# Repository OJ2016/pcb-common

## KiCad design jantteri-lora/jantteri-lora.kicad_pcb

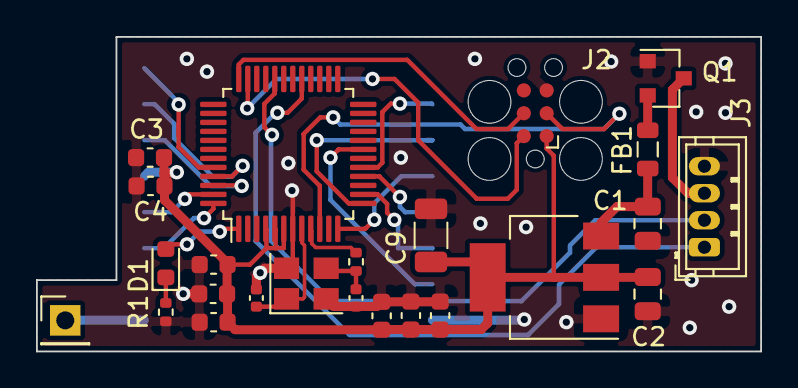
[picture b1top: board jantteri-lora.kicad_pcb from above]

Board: 2 copper layers, 40.2 x 17.5 mm, 25 parts (1 on the bottom side), 27 nets.

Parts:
C1, C2: 10u; C_0805_2012Metric
C3, C4, C10, C11, C12, C13, C14, C15: 100n; C_0603_1608Metric
C9: 4u7; C_1206_3216Metric
C16, C17: 12p; C_0402_1005Metric
D1: LED; LED_0603_1608Metric
FB1: GZ2012D101TF; L_0805_2012Metric
J1: ANT; PinHeader_1x01_P2.54mm_Vertical
J2: Conn_02x03_Odd_Even; Tag-Connect_TC2030-IDC-FP_2x03_P1.27mm_Vertical
J3: DBG; JST_ZH_B4B-ZR_1x04_P1.50mm_Vertical
Q1: IRLML6402TRPBF; SOT-23
R1: 1k5; R_0402_1005Metric
R2: 47; R_0402_1005Metric
U2: AMS1117-3.3; SOT-223-3_TabPin2
U3: RFM95W-868S2; HOPERF_RFM9XW_SMD
U6: STM32G030C8T6; LQFP-48_7x7mm_P0.5mm
Y1: 16MHz; Crystal_SMD_3225-4Pin_3.2x2.5mm

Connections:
+3V3: C2.1, C3.1, C4.1, C9.1, C10.1, C11.1, C12.1, C13.1, C14.1, C15.1, J2.1, U2.2, U3.13, U6.4, U6.5, U6.6
/AMS1117-3.3/VIN: C1.1, FB1.1, U2.3
/STM32G030C8T6/HSE_IN: C16.1, U6.8, Y1.1
/STM32G030C8T6/HSE_OUT: R2.1, U6.9
/STM32G030C8T6/NRST: J2.3, U6.10
/STM32G030C8T6/SWCLK: J2.4, U6.36
/STM32G030C8T6/SWDIO: J2.2, U6.35
DBG_RX: J3.2, U6.32
DBG_TX: J3.1, U6.29
GND: C1.2, C2.2, C3.2, C4.2, C9.2, C10.2, C11.2, C12.2, C13.2, C14.2, C15.2, C16.2, C17.2, J2.5, J3.4, Q1.1, R1.1, U2.1, U3.1, U3.8, U3.10, U6.7, Y1.2, Y1.4
unnamed: C17.1, R2.2, Y1.3
unnamed: D1.1, R1.2
unnamed: D1.2, U6.1
unnamed: FB1.2, Q1.2
unnamed: J1.1, U3.9
RFM_DIO0: U3.14, U6.46
RFM_DIO1: U3.15, U6.45
RFM_DIO2: U3.16, U6.44
RFM_DIO3: U3.11, U6.48
RFM_DIO4: U3.12, U6.47
RFM_DIO5: U3.7, U6.19
RFM_NSS: U3.5, U6.16
RFM_RST: U3.6, U6.14
SPI1_MISO: U3.2, U6.17
SPI1_MOSI: U3.3, U6.13
SPI1_SCK: U3.4, U6.12
USB-5V: J3.3, Q1.3

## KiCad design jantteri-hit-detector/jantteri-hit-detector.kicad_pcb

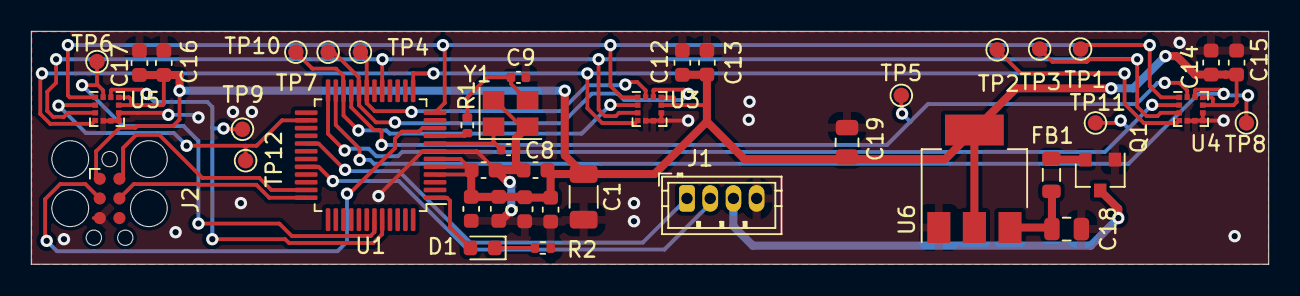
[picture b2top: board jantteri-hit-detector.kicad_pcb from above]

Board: 2 copper layers, 79.9 x 15.0 mm, 42 parts (0 on the bottom side), 27 nets.

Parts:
C1: 4u7; C_1206_3216Metric
C2, C3, C4, C5, C6, C7, C12, C13, C14, C15, C16, C17: 100n; C_0603_1608Metric
C8, C9: 12p; C_0402_1005Metric
C18, C19: 10u; C_0805_2012Metric
D1: LED; LED_0603_1608Metric
FB1: GZ2012D101TF; L_0805_2012Metric
J1: Conn_01x04_Male; JST_ZH_B4B-ZR_1x04_P1.50mm_Vertical
J2: Conn_02x03_Odd_Even; Tag-Connect_TC2030-IDC-FP_2x03_P1.27mm_Vertical
Q1: IRLML6402TRPBF; SOT-23
R1: 47; R_0402_1005Metric
R2: 1k5; R_0402_1005Metric
TP1, TP2, TP3, TP4, TP5, TP6, TP7, TP8, TP9, TP10, TP11, TP12: TestPoint; TestPoint_Pad_D1.0mm
U1: STM32G030C8T6; LQFP-48_7x7mm_P0.5mm
U3, U4, U5: LIS2DW12TR; LGA-12_2x2mm_P0.5mm
U6: AMS1117-3.3; SOT-223-3_TabPin2
Y1: 16MHz; Crystal_SMD_3225-4Pin_3.2x2.5mm

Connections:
+3V3: C1.1, C2.1, C3.1, C4.1, C5.1, C6.1, C7.1, C12.1, C13.1, C14.1, C15.1, C16.1, C17.1, C19.1, J2.1, U1.4 (VBAT), U1.5 (VREF+), U1.6 (VDD/VDDA), U3.9 (VDD), U3.10 (VDD_IO), U4.9 (VDD), U4.10 (VDD_IO), U5.9 (VDD), U5.10 (VDD_IO), U6.2 (VO)
/AMS1117-3.3/VIN: C18.1, FB1.1, U6.3 (VI)
/STM32G030C8T6/HSE_IN: C8.1, U1.8 (PF0-OSC_IN), Y1.1
/STM32G030C8T6/HSE_OUT: R1.1, U1.9 (PF1-OSC_OUT)
/STM32G030C8T6/NRST: J2.3, U1.10 (NRST)
/STM32G030C8T6/SWCLK: J2.4, U1.36 (PA14-BOOT0_(SWCLK))
/STM32G030C8T6/SWDIO: J2.2, U1.35 (PA13_(SWDIO))
GND: C1.2, C2.2, C3.2, C4.2, C5.2, C6.2, C7.2, C8.2, C9.2, C12.2, C13.2, C14.2, C15.2, C16.2, C17.2, C18.2, C19.2, J1.4, J2.5, Q1.1 (G), R2.1, U1.7 (VSS/VSSA), U3.5 (NC), U3.6 (GND), U3.7 (RES), U3.8 (GND), U4.5 (NC), U4.6 (GND), U4.7 (RES), U4.8 (GND), U5.5 (NC), U5.6 (GND), U5.7 (RES), U5.8 (GND), U6.1 (GND), Y1.2, Y1.4
HIT_RX: J1.2, U1.32 (PA10)
HIT_TX: J1.1, U1.29 (PA9)
KX1_CS: TP10.1, U1.22 (PB10), U3.2 (CS)
KX1_INT1: TP4.1, U1.19 (PB0), U3.12 (INT1)
KX1_INT2: TP7.1, U1.20 (PB1), U3.11 (INT2)
KX2_CS: TP11.1, U1.24 (PB12), U4.2 (CS)
KX2_INT1: TP5.1, U1.21 (PB2), U4.12 (INT1)
KX2_INT2: TP8.1, U1.23 (PB11), U4.11 (INT2)
KX3_CS: TP12.1, U1.26 (PB14), U5.2 (CS)
KX3_INT1: TP6.1, U1.43 (PB4), U5.12 (INT1)
KX3_INT2: TP9.1, U1.44 (PB5), U5.11 (INT2)
KX_MISO: TP3.1, U1.17 (PA6), U3.3 (SDO/SA0), U4.3 (SDO/SA0), U5.3 (SDO/SA0)
KX_MOSI: TP2.1, U1.13 (PA2), U3.4 (SDA/SDI/SDO), U4.4 (SDA/SDI/SDO), U5.4 (SDA/SDI/SDO)
KX_SCLK: TP1.1, U1.12 (PA1), U3.1 (SCL/SPC), U4.1 (SCL/SPC), U5.1 (SCL/SPC)
unnamed: C9.1, R1.2, Y1.3
unnamed: D1.2 (A), U1.1 (PC13)
unnamed: D1.1 (K), R2.2
unnamed: FB1.2, Q1.2 (S)
VCC: J1.3, Q1.3 (D)

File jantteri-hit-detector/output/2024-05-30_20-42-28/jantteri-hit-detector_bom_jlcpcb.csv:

Comment,Designator,Footprint,LCSC
100n,"C2,C3,C4,C5,C6,C7,C12,C13,C14,C15,C16,C17",Capacitor_SMD:C_0603_1608Metric,C14663
10u,"C18,C19",Capacitor_SMD:C_0805_2012Metric,C15850
12p,"C8,C9",Capacitor_SMD:C_0402_1005Metric,C1547
16MHz,Y1,Crystal:Crystal_SMD_3225-4Pin_3.2x2.5mm,C13738
1k5,R2,Resistor_SMD:R_0402_1005Metric,C25867
47,R1,Resistor_SMD:R_0402_1005Metric,C25118
4u7,C1,Capacitor_SMD:C_1206_3216Metric,C29823
AMS1117-3.3,U6,Package_TO_SOT_SMD:SOT-223-3_TabPin2,C6186
GZ2012D101TF,FB1,Inductor_SMD:L_0805_2012Metric,C1015
IRLML6402TRPBF,Q1,Package_TO_SOT_SMD:SOT-23,C2593
LED,D1,LED_SMD:LED_0603_1608Metric,C2286
LIS2DW12TR,"U3,U4,U5",Package_LGA:LGA-12_2x2mm_P0.5mm,C189624
STM32G030C8T6,U1,Package_QFP:LQFP-48_7x7mm_P0.5mm,C529329

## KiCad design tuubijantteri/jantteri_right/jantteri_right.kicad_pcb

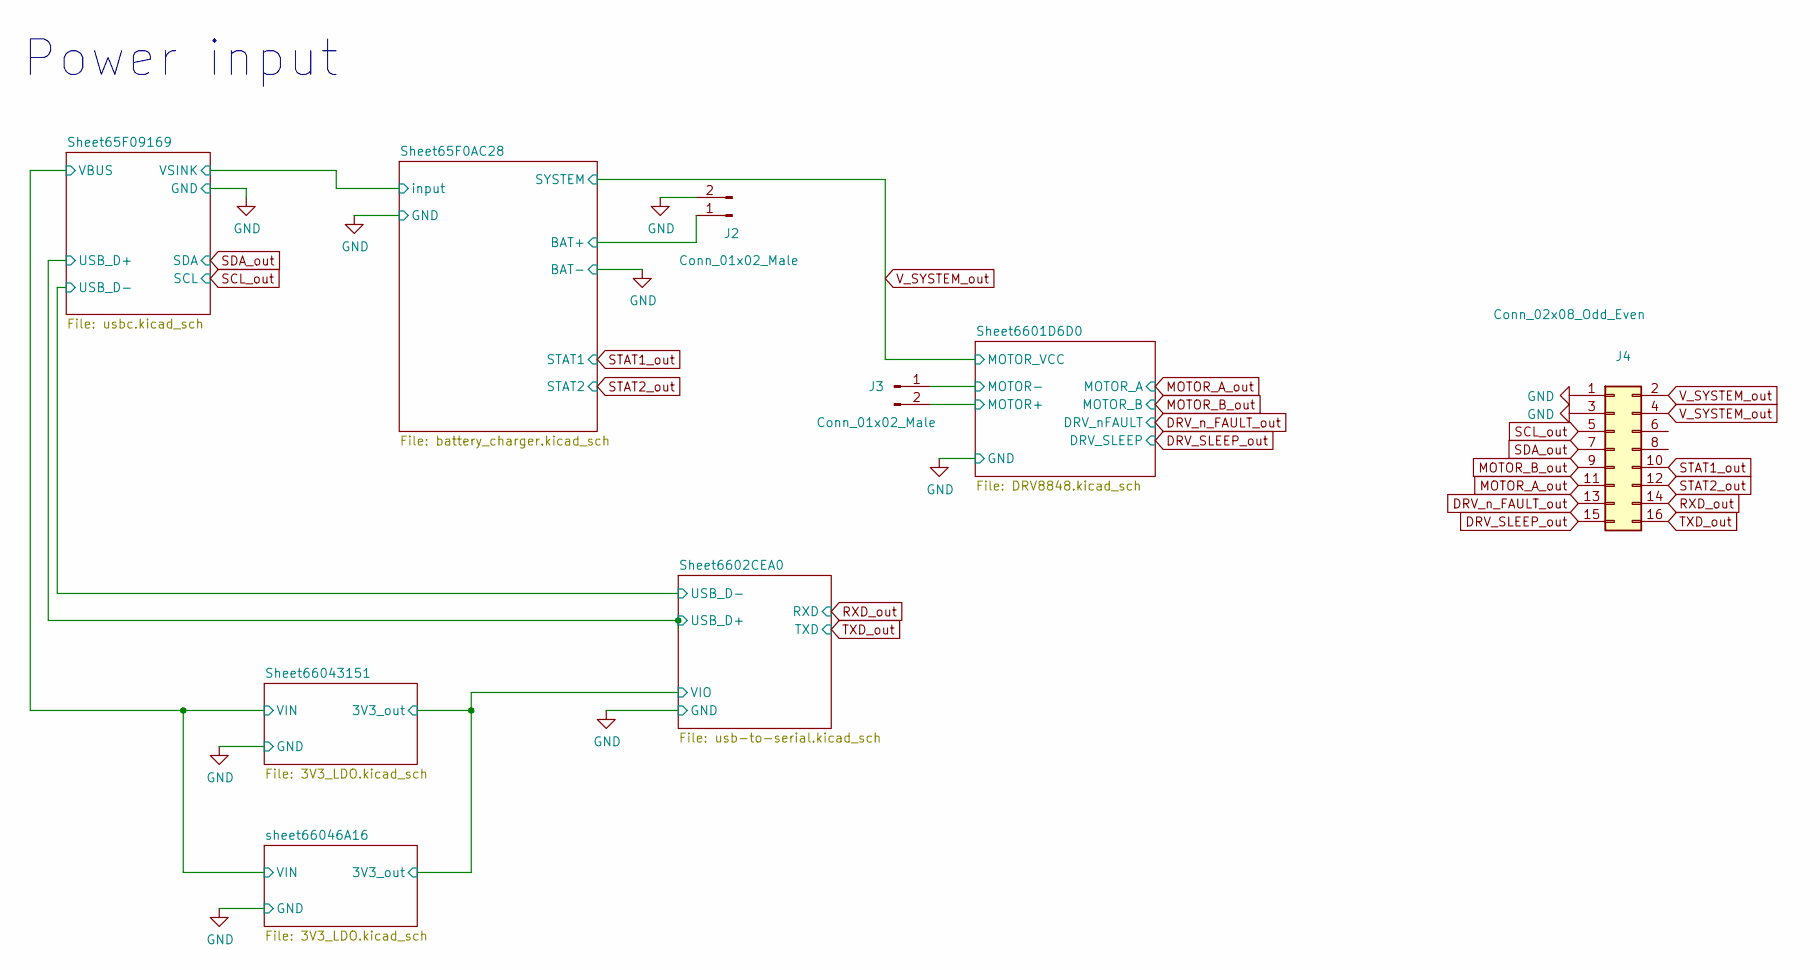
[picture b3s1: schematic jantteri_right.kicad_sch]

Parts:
J2, J3: Conn_01x02_Male; JST_VH_B2P-VH-B_1x02_P3.96mm_Vertical; LCSC C160315
J4: Conn_02x08_Odd_Even; PinHeader_2x08_P1.27mm_Vertical_SMD; LCSC C178295

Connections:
/Sheet65F0AC28/BAT+: J2.1; also elsewhere on the board
/Sheet6601D6D0/MOTOR+: J3.2; also elsewhere on the board
/Sheet6601D6D0/MOTOR-: J3.1; also elsewhere on the board
DRV_SLEEP_out: J4.15; also elsewhere on the board
DRV_n_FAULT_out: J4.13; also elsewhere on the board
GND: J2.2, J4.1, J4.3; also elsewhere on the board
MOTOR_A_out: J4.11; also elsewhere on the board
MOTOR_B_out: J4.9; also elsewhere on the board
RXD_out: J4.14; also elsewhere on the board
SCL_out: J4.5; also elsewhere on the board
SDA_out: J4.7; also elsewhere on the board
STAT1_out: J4.10; also elsewhere on the board
STAT2_out: J4.12; also elsewhere on the board
TXD_out: J4.16; also elsewhere on the board
V_SYSTEM_out: J4.2, J4.4; also elsewhere on the board

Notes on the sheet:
Power input

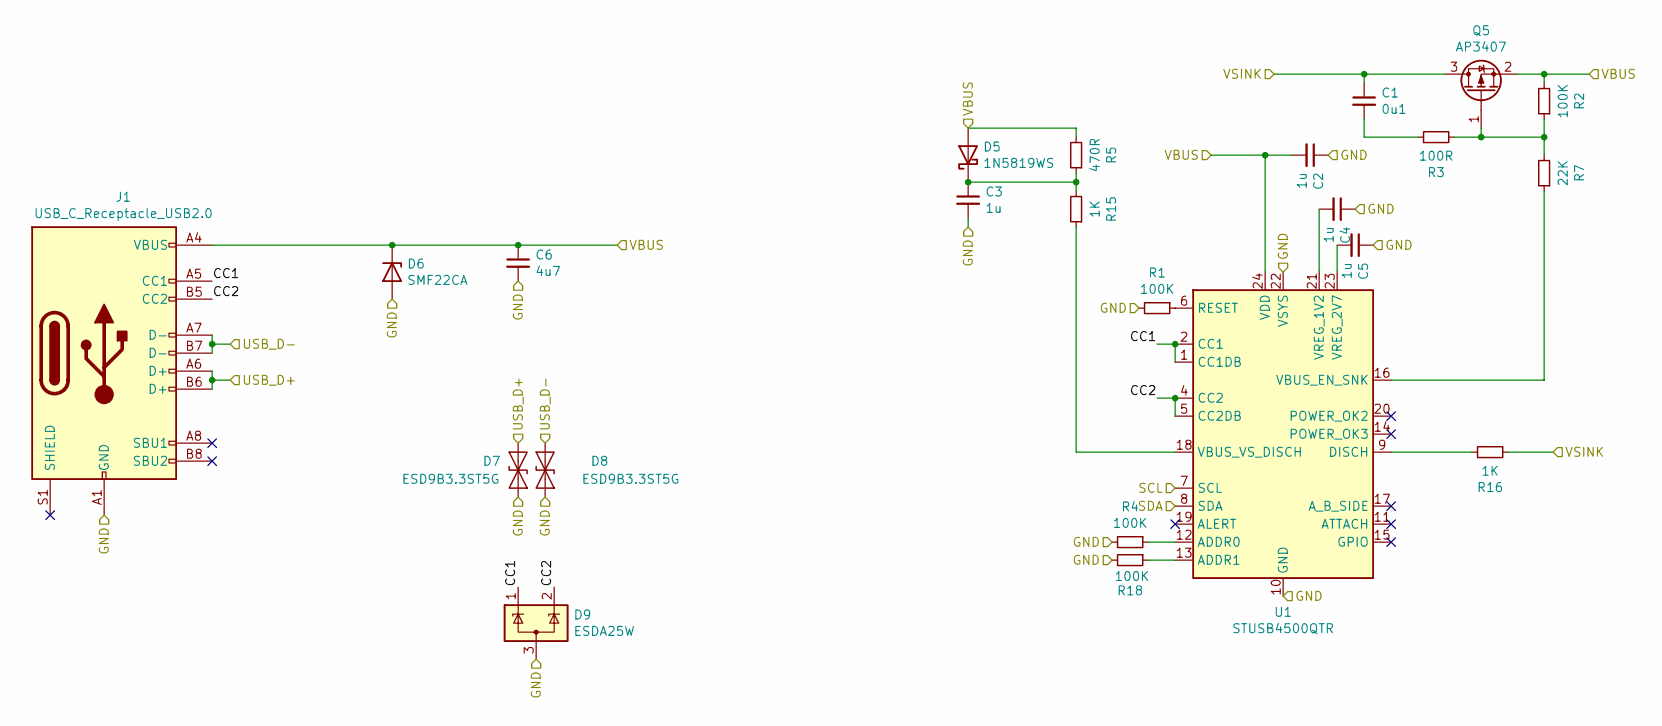
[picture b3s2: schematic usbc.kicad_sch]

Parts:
C1: 0u1; C_0402_1005Metric; LCSC C307331
C2, C3, C4, C5: 1u; C_0402_1005Metric; LCSC C52923
C6: 4u7; C_1206_3216Metric; LCSC C29823
D5: 1N5819WS; D_SOD-323; LCSC C191023
D6: SMF22CA; D_SOD-123F; LCSC C123807
D7, D8: ESD9B3.3ST5G; D_SOD-923; LCSC C96512
D9: ESDA25W; SOT-323_SC-70; LCSC C3021136
J1: USB_C_Receptacle_USB2.0; USB_C_Receptacle_JAE_DX07S024WJ3R400; LCSC C309367
Q5: AP3407; SOT-23; LCSC C353080
R1, R2, R4, R18: 100K; R_0402_1005Metric; LCSC C25741
R3: 100R; R_0603_1608Metric; LCSC C22775
R5: 470R; R_0603_1608Metric; LCSC C23179
R7: 22K; R_0603_1608Metric; LCSC C31850
R15, R16: 1K; R_0603_1608Metric; LCSC C21190
U1: STUSB4500QTR; QFN-24-1EP_4x4mm_P0.5mm_EP2.7x2.7mm; LCSC C2678061

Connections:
/Sheet65F09169/CC1: D9.1 (K), J1.A5 (CC1), U1.1 (CC1DB), U1.2 (CC1)
/Sheet65F09169/CC2: D9.2 (K), J1.B5 (CC2), U1.4 (CC2), U1.5 (CC2DB)
/Sheet65F09169/USB_D+: D7.1 (A1), J1.A6 (D+), J1.B6 (D+); also elsewhere on the board
/Sheet65F09169/USB_D-: D8.1 (A1), J1.A7 (D-), J1.B7 (D-); also elsewhere on the board
/Sheet65F09169/VBUS: C2.2, C6.1, D5.2 (A), D6.1 (K), J1.A4 (VBUS), J1.A9 (VBUS), J1.B4 (VBUS), J1.B9 (VBUS), Q5.2 (S), R2.2, R5.2, U1.24 (VDD); also elsewhere on the board
/Sheet65F09169/VSINK: C1.1, Q5.3 (D), R16.2; also elsewhere on the board
GND: C2.1, C3.2, C4.1, C5.1, C6.2, D6.2 (A), D7.2 (A2), D8.2 (A2), D9.3 (A), J1.A1 (GND), J1.A12 (GND), J1.B1 (GND), J1.B12 (GND), R1.2, R4.2, R18.2, U1.10 (GND), U1.22 (VSYS), U1.25 (GND); also elsewhere on the board
unnamed: C1.2, R3.1
unnamed: C3.1, D5.1 (K), R5.1, R15.2
unnamed: Q5.1 (G), R2.1, R3.2, R7.2
unnamed: R4.1, U1.12 (ADDR0)
unnamed: R18.1, U1.13 (ADDR1)
unnamed: R16.1, U1.9 (DISCH)
unnamed: R1.1, U1.6 (RESET)
unnamed: R7.1, U1.16 (VBUS_EN_SNK)
unnamed: R15.1, U1.18 (VBUS_VS_DISCH)
unnamed: C4.2, U1.21 (VREG_1V2)
unnamed: C5.2, U1.23 (VREG_2V7)
SCL_out: U1.7 (SCL); also elsewhere on the board
SDA_out: U1.8 (SDA); also elsewhere on the board

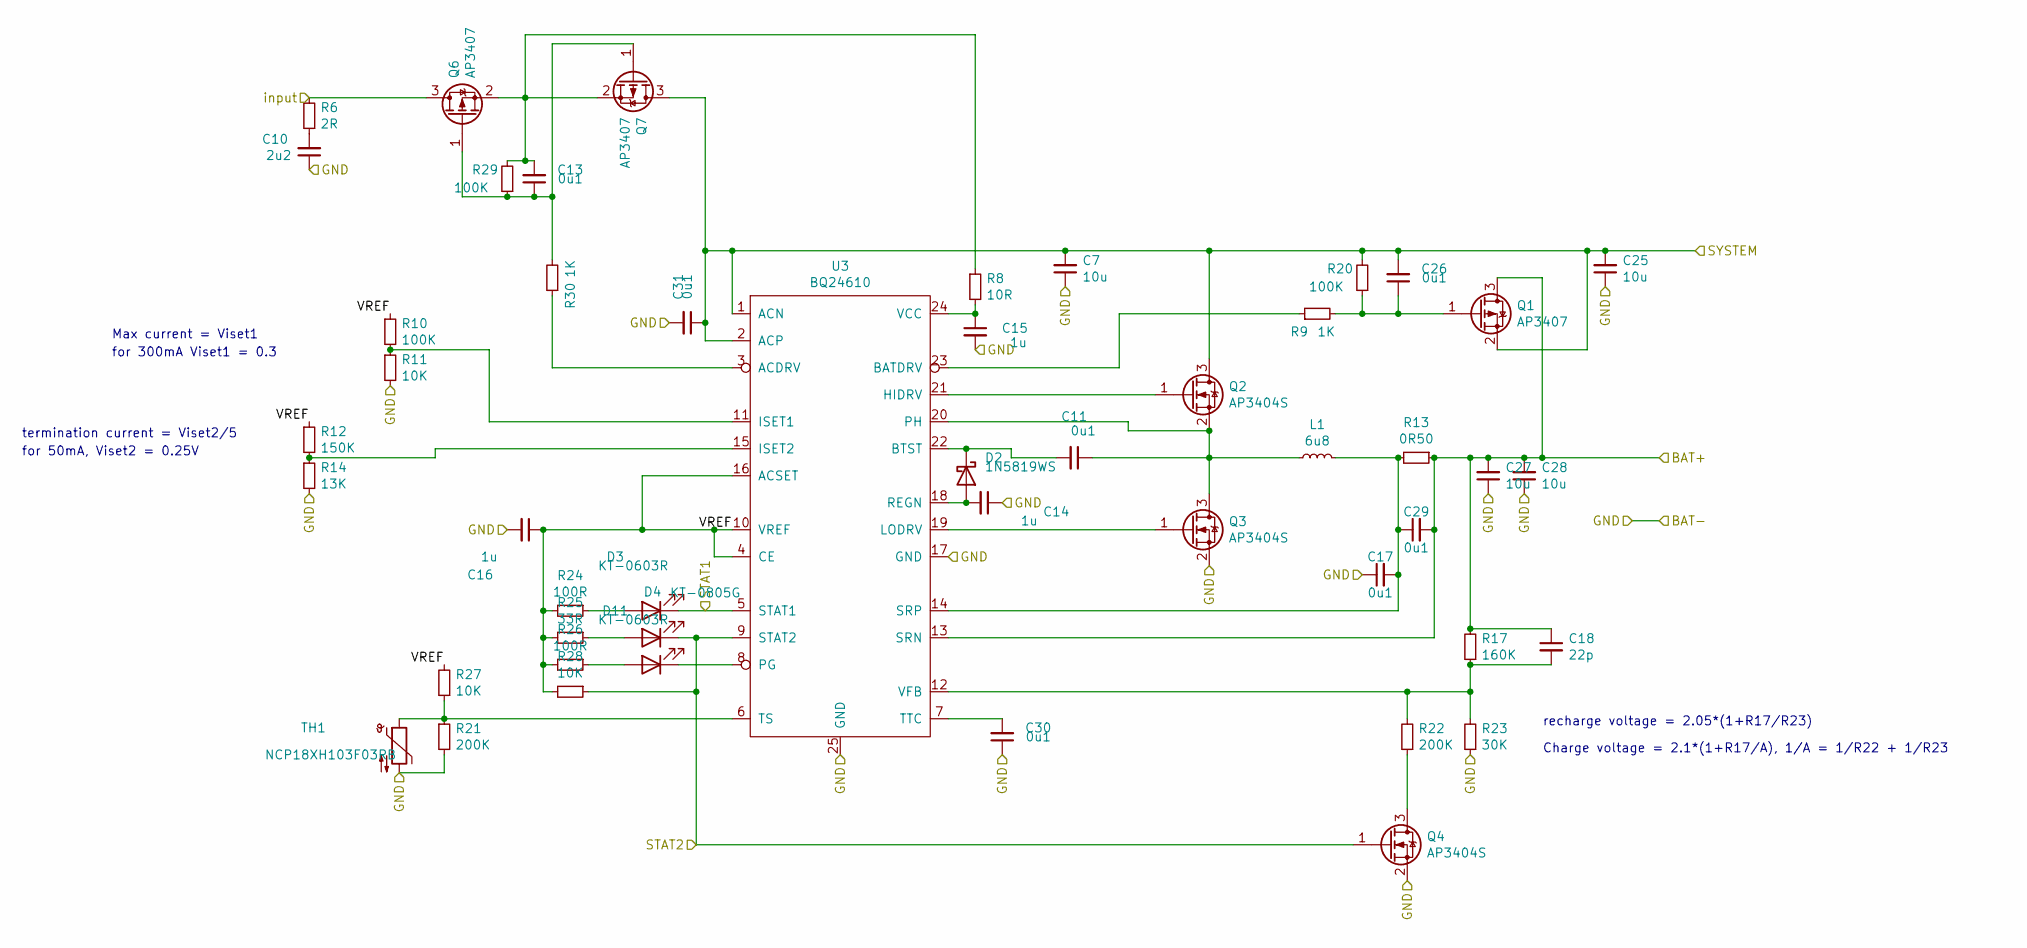
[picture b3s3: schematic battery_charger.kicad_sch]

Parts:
C7, C25, C27, C28: 10u; C_1206_3216Metric; LCSC C13585
C10: 2u2; C_0805_2012Metric; LCSC C377773
C11, C13, C17, C26, C29, C30, C31: 0u1; C_0603_1608Metric; LCSC C14663
C14, C15: 1u; C_0603_1608Metric; LCSC C15849
C16: 1u; C_0402_1005Metric; LCSC C52923
C18: 22p; C_0805_2012Metric; LCSC C107145
D2: 1N5819WS; D_SOD-323; LCSC C191023
D3, D11: KT-0603R; D_0603_1608Metric; LCSC C2286
D4: KT-0805G; D_0805_2012Metric; LCSC C2297
L1: 6u8; L_Abracon_ASPI-0630LR; LCSC C167221
Q1, Q6, Q7: AP3407; SOT-23; LCSC C353080
Q2, Q3, Q4: AP3404S; SOT-23; LCSC C2875959
R6: 2R; R_0603_1608Metric; LCSC C22977
R8: 10R; R_0603_1608Metric; LCSC C22859
R9, R30: 1K; R_0402_1005Metric; LCSC C11702
R10, R20, R29: 100K; R_0402_1005Metric; LCSC C25741
R11, R27, R28: 10K; R_0402_1005Metric; LCSC C25744
R12: 150K; R_0603_1608Metric; LCSC C22807
R13: 0R50; R_2512_6332Metric; LCSC C2941069
R14: 13K; R_0603_1608Metric; LCSC C22797
R17: 160K; R_0402_1005Metric; LCSC C321320
R21, R22: 200K; R_0402_1005Metric; LCSC C25764
R23: 30K; R_0402_1005Metric; LCSC C138008
R24, R26: 100R; R_0402_1005Metric; LCSC C25076
R25: 33R; R_0402_1005Metric; LCSC C25105
TH1: NCP18XH103F03RB; R_0603_1608Metric; LCSC C13564
U3: BQ24610; QFN-24-1EP_4x4mm_P0.5mm_EP2.8x2.8mm; LCSC C19384

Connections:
/Sheet65F0AC28/BAT+: C18.1, C27.2, C28.2, C29.2, Q1.3 (D), R13.1, R17.2, U3.13 (SRN); also elsewhere on the board
/Sheet65F0AC28/VREF: C16.1, R10.1, R12.1, R24.2, R25.2, R26.2, R27.2, R28.2, U3.4 (CE), U3.10 (VREF), U3.16 (ACSET)
/Sheet65F09169/VSINK: Q6.3 (D), R6.2; also elsewhere on the board
GND: C7.1, C10.1, C14.1, C15.2, C16.2, C17.1, C25.1, C27.1, C28.1, C30.1, C31.2, Q3.2 (S), Q4.2 (S), R11.2, R14.2, R21.2, R23.1, TH1.2, U3.17 (GND), U3.25 (GND); also elsewhere on the board
unnamed: C10.2, R6.1
unnamed: C14.2, D2.2 (A), U3.18 (REGN)
unnamed: C11.2, D2.1 (K), U3.22 (BTST)
unnamed: D3.2 (A), R24.1
unnamed: D4.2 (A), R25.1
unnamed: D11.2 (A), R26.1
unnamed: D11.1 (K), U3.8 (PG)
unnamed: C26.1, Q1.1 (G), R9.2, R20.1
unnamed: Q2.1 (G), U3.21 (HIDRV)
unnamed: C11.1, L1.1, Q2.2 (S), Q3.3 (D), U3.20 (PH)
unnamed: Q3.1 (G), U3.19 (LODRV)
unnamed: Q4.3 (D), R22.1
unnamed: C13.1, Q6.1 (G), Q7.1 (G), R29.1, R30.2
unnamed: C13.2, Q6.2 (S), Q7.2 (S), R8.1, R29.2
unnamed: R30.1, U3.3 (ACDRV)
unnamed: R9.1, U3.23 (BATDRV)
unnamed: R10.2, R11.1, U3.11 (ISET1)
unnamed: R12.2, R14.1, U3.15 (ISET2)
unnamed: C17.2, C29.1, L1.2, R13.2, U3.14 (SRP)
unnamed: R21.1, R27.1, TH1.1, U3.6 (TS)
unnamed: C30.2, U3.7 (TTC)
unnamed: C15.1, R8.2, U3.24 (VCC)
unnamed: C18.2, R17.1, R22.2, R23.2, U3.12 (VFB)
STAT1_out: D3.1 (K), U3.5 (STAT1); also elsewhere on the board
STAT2_out: D4.1 (K), Q4.1 (G), R28.1, U3.9 (STAT2); also elsewhere on the board
V_SYSTEM_out: C7.2, C25.2, C26.2, C31.1, Q1.2 (S), Q2.3 (D), Q7.3 (D), R20.2, U3.1 (ACN), U3.2 (ACP); also elsewhere on the board

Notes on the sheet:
for 300mA Viset1 = 0.3
termination current = Viset2/5
recharge voltage = 2.05*(1+R17/R23)
for 50mA, Viset2 = 0.25V
Charge voltage = 2.1*(1+R17/A), 1/A = 1/R22 + 1/R23
Max current = Viset1

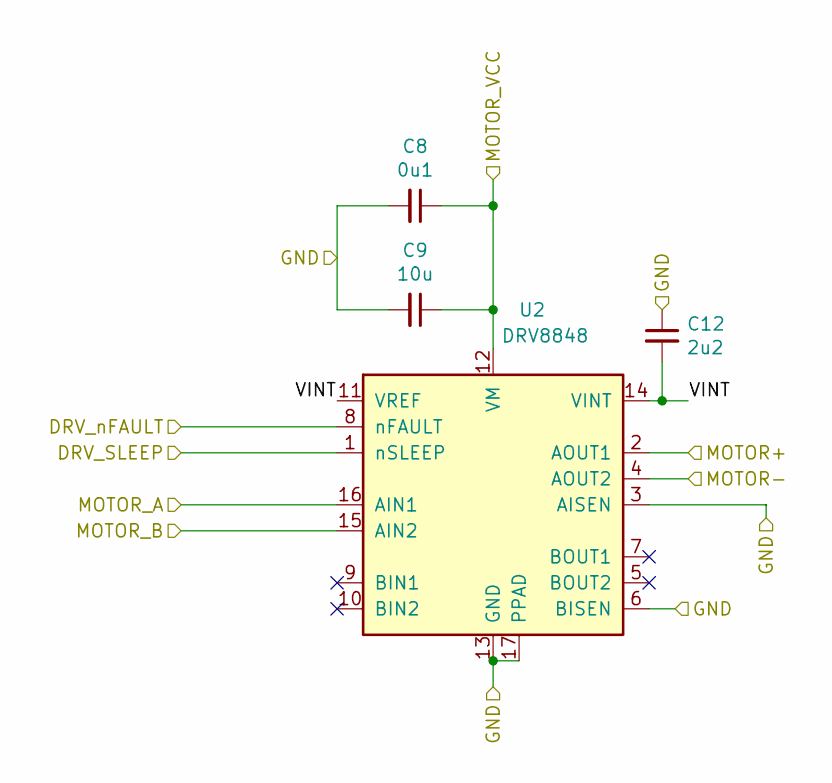
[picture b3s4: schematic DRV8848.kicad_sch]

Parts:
C8: 0u1; C_0603_1608Metric; LCSC C14663
C9: 10u; C_0805_2012Metric; LCSC C15850
C12: 2u2; C_0805_2012Metric; LCSC C377773
U2: DRV8848; TSSOP-16-1EP_4.4x5mm_P0.65mm; LCSC C131079

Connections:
/Sheet6601D6D0/MOTOR+: U2.2 (AOUT1); also elsewhere on the board
/Sheet6601D6D0/MOTOR-: U2.4 (AOUT2); also elsewhere on the board
/Sheet6601D6D0/VINT: C12.2, U2.11 (VREF), U2.14 (VINT)
DRV_SLEEP_out: U2.1 (nSLEEP); also elsewhere on the board
DRV_n_FAULT_out: U2.8 (nFAULT); also elsewhere on the board
GND: C8.2, C9.2, C12.1, U2.3 (AISEN), U2.6 (BISEN), U2.13 (GND), U2.17 (PPAD); also elsewhere on the board
MOTOR_A_out: U2.16 (AIN1); also elsewhere on the board
MOTOR_B_out: U2.15 (AIN2); also elsewhere on the board
V_SYSTEM_out: C8.1, C9.1, U2.12 (VM); also elsewhere on the board

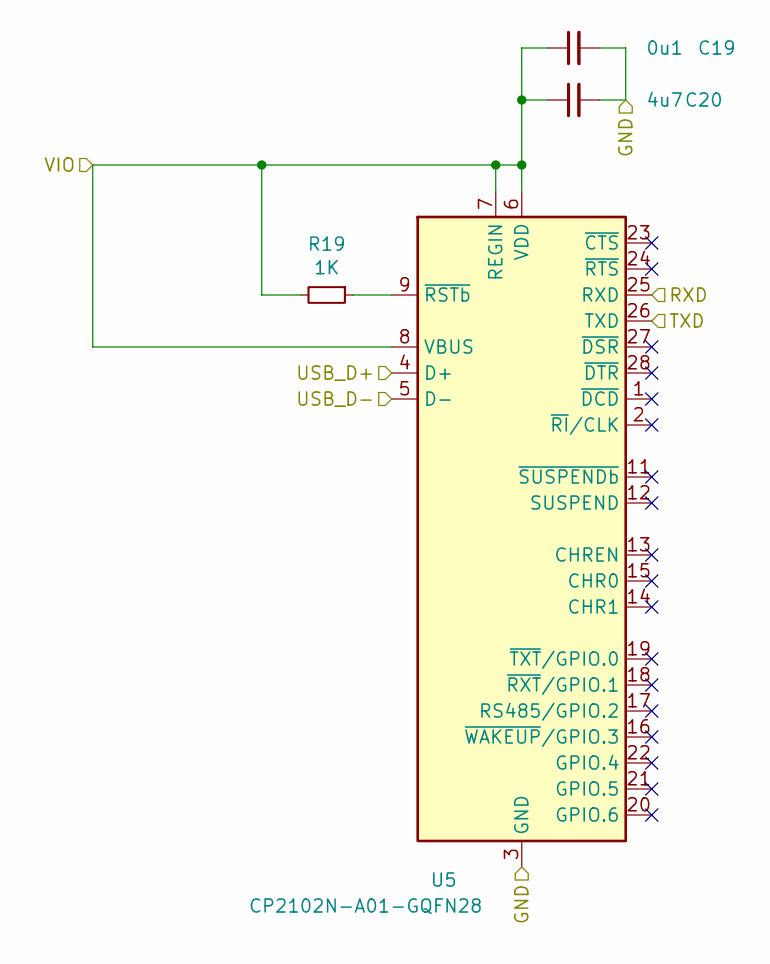
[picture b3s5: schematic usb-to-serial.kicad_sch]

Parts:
C19: 0u1; C_0402_1005Metric; LCSC C1525
C20: 4u7; C_0402_1005Metric; LCSC C23733
R19: 1K; R_0402_1005Metric; LCSC C11702
U5: CP2102N-A01-GQFN28; QFN-28-1EP_5x5mm_P0.5mm_EP3.35x3.35mm; LCSC C964632

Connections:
/Sheet65F09169/USB_D+: U5.4 (D+); also elsewhere on the board
/Sheet65F09169/USB_D-: U5.5 (D-); also elsewhere on the board
/Sheet6602CEA0/VIO: C19.1, C20.1, R19.2, U5.6 (VDD), U5.7 (REGIN), U5.8 (VBUS); also elsewhere on the board
GND: C19.2, C20.2, U5.3 (GND), U5.29 (GND); also elsewhere on the board
unnamed: R19.1, U5.9 (~RSTb)
RXD_out: U5.25 (RXD); also elsewhere on the board
TXD_out: U5.26 (TXD); also elsewhere on the board

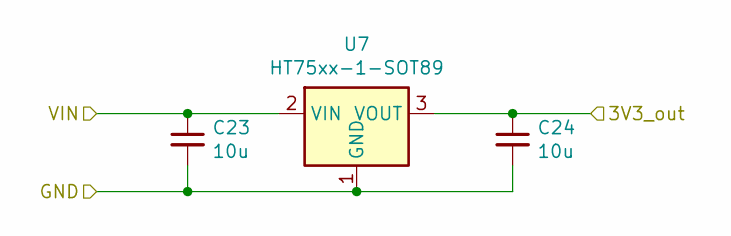
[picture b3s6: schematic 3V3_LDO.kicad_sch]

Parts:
C23, C24: 10u; C_0805_2012Metric; LCSC C440198
U7: HT75xx-1-SOT89; SOT-89-3; LCSC C14289

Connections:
/Sheet65F09169/VBUS: C23.1, U7.2 (VIN); also elsewhere on the board
/Sheet6602CEA0/VIO: C24.1, U7.3 (VOUT); also elsewhere on the board
GND: C23.2, C24.2, U7.1 (GND); also elsewhere on the board

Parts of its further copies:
C21, C22: 10u; C_0805_2012Metric; LCSC C440198
U6: HT75xx-1-SOT89; SOT-89-3; LCSC C14289

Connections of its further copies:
/Sheet65F09169/VBUS: C21.1, U6.2 (VIN); also elsewhere on the board
/Sheet6602CEA0/VIO: C22.1, U6.3 (VOUT); also elsewhere on the board
GND: C21.2, C22.2, U6.1 (GND); also elsewhere on the board

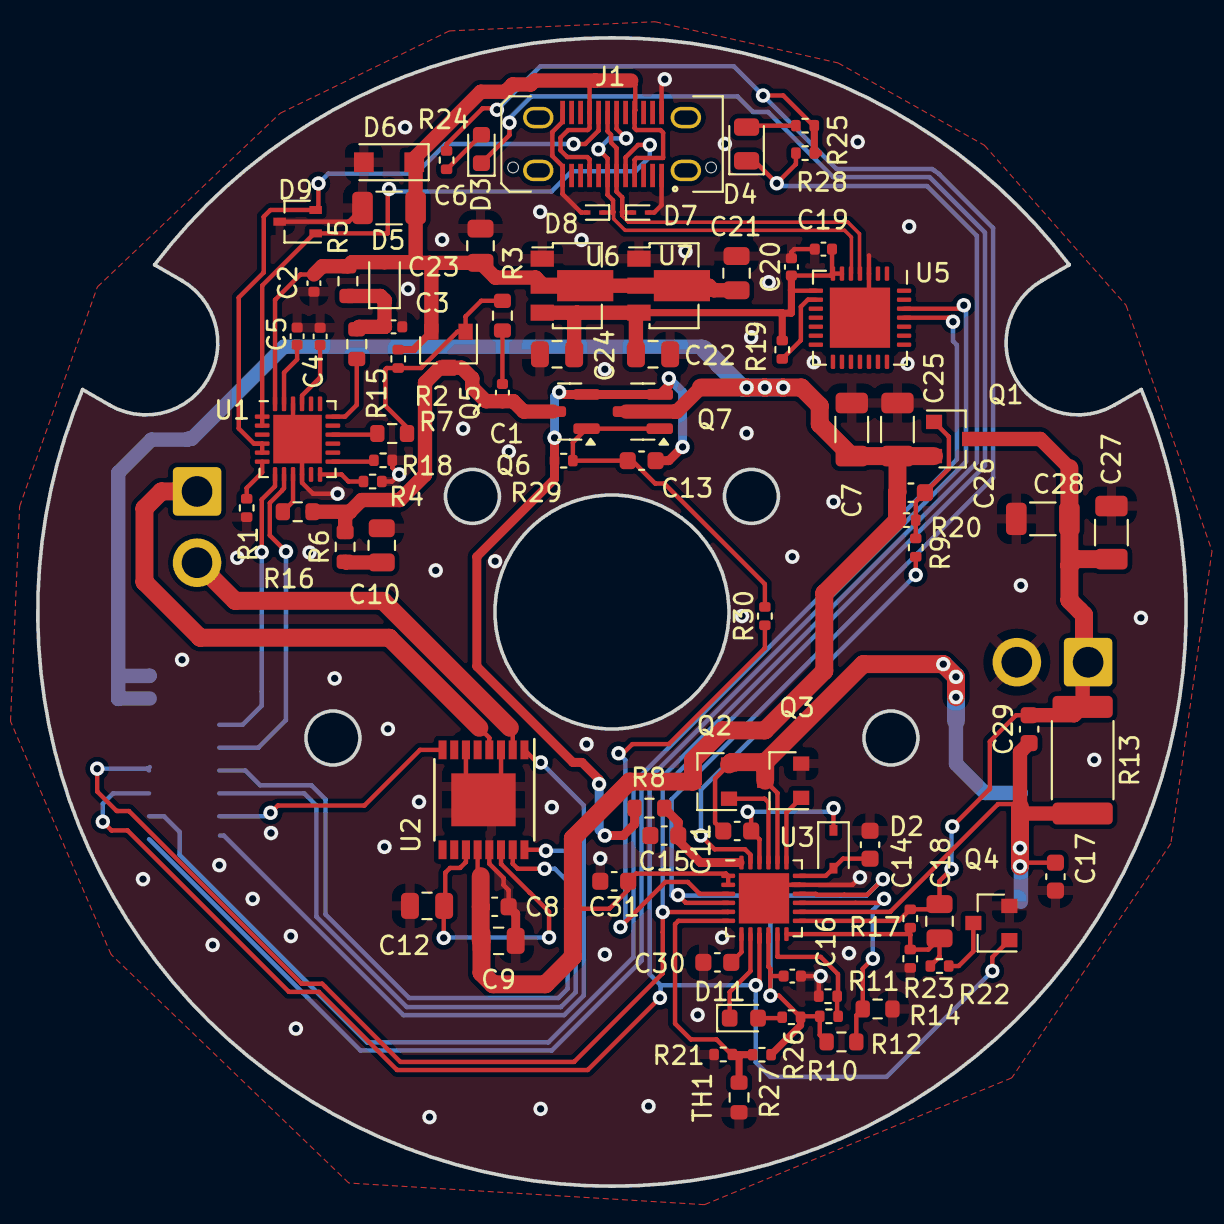
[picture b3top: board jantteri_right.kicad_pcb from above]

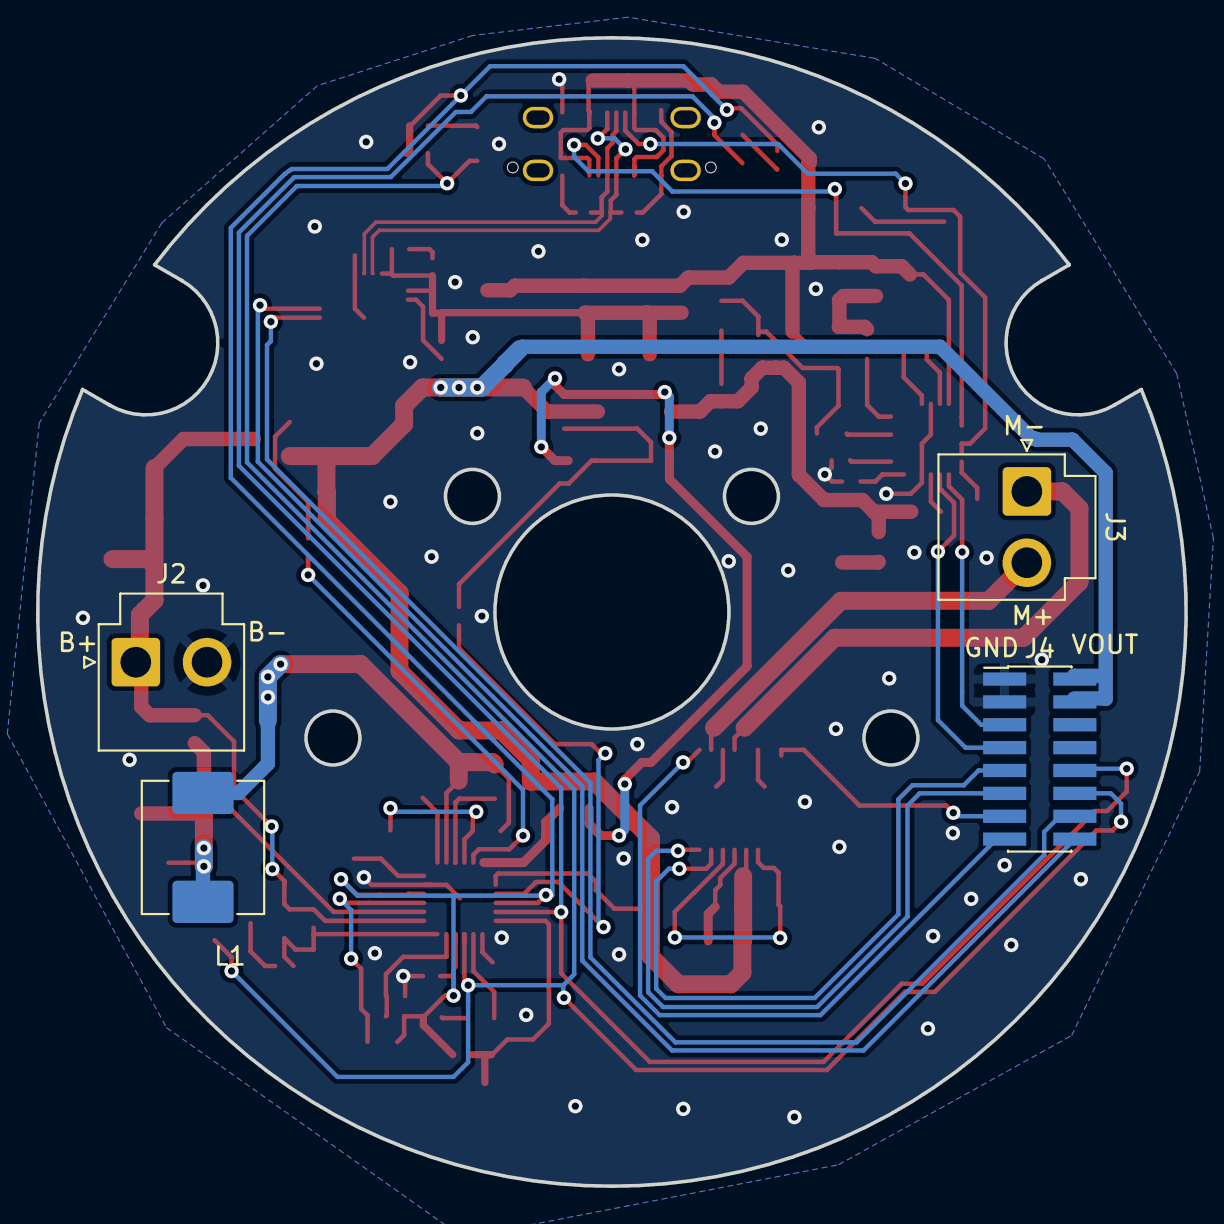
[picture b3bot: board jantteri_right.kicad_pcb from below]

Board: 2 copper layers, 63.8 x 63.8 mm, 89 parts (4 on the bottom side), 59 nets.

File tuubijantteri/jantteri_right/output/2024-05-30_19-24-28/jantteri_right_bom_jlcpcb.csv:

Comment,Designator,Footprint,LCSC
0R50,R13,Resistor_SMD:R_2512_6332Metric,C2941069
0u1,C1,Capacitor_SMD:C_0402_1005Metric,C307331
0u1,"C11,C13,C17,C26,C29,C30,C31,C8",Capacitor_SMD:C_0603_1608Metric,C14663
0u1,C19,Capacitor_SMD:C_0402_1005Metric,C1525
100K,"R1,R2,R4,R18,R10,R20,R29",Resistor_SMD:R_0402_1005Metric,C25741
100R,R3,Resistor_SMD:R_0603_1608Metric,C22775
100R,"R24,R26",Resistor_SMD:R_0402_1005Metric,C25076
10K,"R11,R27,R28",Resistor_SMD:R_0402_1005Metric,C25744
10R,R8,Resistor_SMD:R_0603_1608Metric,C22859
10u,"C21,C22,C23,C24",Capacitor_SMD:C_0805_2012Metric,C440198
10u,"C7,C25,C27,C28",Capacitor_SMD:C_1206_3216Metric,C13585
10u,C9,Capacitor_SMD:C_0805_2012Metric,C15850
13K,R14,Resistor_SMD:R_0603_1608Metric,C22797
150K,R12,Resistor_SMD:R_0603_1608Metric,C22807
160K,R17,Resistor_SMD:R_0402_1005Metric,C321320
1K,"R15,R16",Resistor_SMD:R_0603_1608Metric,C21190
1K,"R9,R30,R19",Resistor_SMD:R_0402_1005Metric,C11702
1N5819WS,"D5,D2",Diode_SMD:D_SOD-323,C191023
1u,"C2,C3,C4,C5,C16",Capacitor_SMD:C_0402_1005Metric,C52923
1u,"C14,C15",Capacitor_SMD:C_0603_1608Metric,C15849
200K,"R21,R22",Resistor_SMD:R_0402_1005Metric,C25764
22K,R7,Resistor_SMD:R_0603_1608Metric,C31850
22p,C18,Capacitor_SMD:C_0805_2012Metric,C107145
2R,R6,Resistor_SMD:R_0603_1608Metric,C22977
2u2,"C10,C12",Capacitor_SMD:C_0805_2012Metric,C377773
30K,R23,Resistor_SMD:R_0402_1005Metric,C138008
33R,R25,Resistor_SMD:R_0402_1005Metric,C25105
470R,R5,Resistor_SMD:R_0603_1608Metric,C23179
4u7,C6,Capacitor_SMD:C_1206_3216Metric,C29823
4u7,C20,Capacitor_SMD:C_0402_1005Metric,C23733
6u8,L1,Inductor_SMD:L_Abracon_ASPI-0630LR,C167221
AP3404S,"Q2,Q3,Q4",Package_TO_SOT_SMD:SOT-23,C2875959
AP3407,"Q5,Q1,Q6,Q7",Package_TO_SOT_SMD:SOT-23,C353080
BQ24610,U3,Package_DFN_QFN:QFN-24-1EP_4x4mm_P0.5mm_EP2.8x2.8mm,C19384
CP2102N-A01-GQFN28,U5,Package_DFN_QFN:QFN-28-1EP_5x5mm_P0.5mm_EP3.35x3.35mm,C964632
Conn_01x02_Male,"J2,J3",Connector_JST2:JST_VH_B2P-VH-B_1x02_P3.96mm_Vertical,C160315
Conn_02x08_Odd_Even,J4,Connector_PinHeader_1.27mm:PinHeader_2x08_P1.27mm_Vertical_SMD,C178295
DRV8848,U2,Package_SO:TSSOP-16-1EP_4.4x5mm_P0.65mm,C131079
ESD9B3.3ST5G,"D7,D8",Diode_SMD:D_SOD-923,C96512
ESDA25W,D9,Package_TO_SOT_SMD:SOT-323_SC-70,C3021136
HT75xx-1-SOT89,"U6,U7",Package_TO_SOT_SMD:SOT-89-3,C14289
KT-0603R,"D3,D11",Diode_SMD:D_0603_1608Metric,C2286
KT-0805G,D4,Diode_SMD:D_0805_2012Metric,C2297
NCP18XH103F03RB,TH1,Resistor_SMD:R_0603_1608Metric,C13564
SMF22CA,D6,Diode_SMD:D_SOD-123F,C123807
STUSB4500QTR,U1,Package_DFN_QFN:QFN-24-1EP_4x4mm_P0.5mm_EP2.7x2.7mm,C2678061
USB_C_Receptacle_USB2.0,J1,Connector_USB:USB_C_Receptacle_JAE_DX07S024WJ3R400,C309367
